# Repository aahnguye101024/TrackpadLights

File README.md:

# TrackpadLights
This project tests out a trackpad IC that I found interesting and creates a light that follows your finger input based on the "trackpad" board. 

## Main Board

## Cap Touch Board

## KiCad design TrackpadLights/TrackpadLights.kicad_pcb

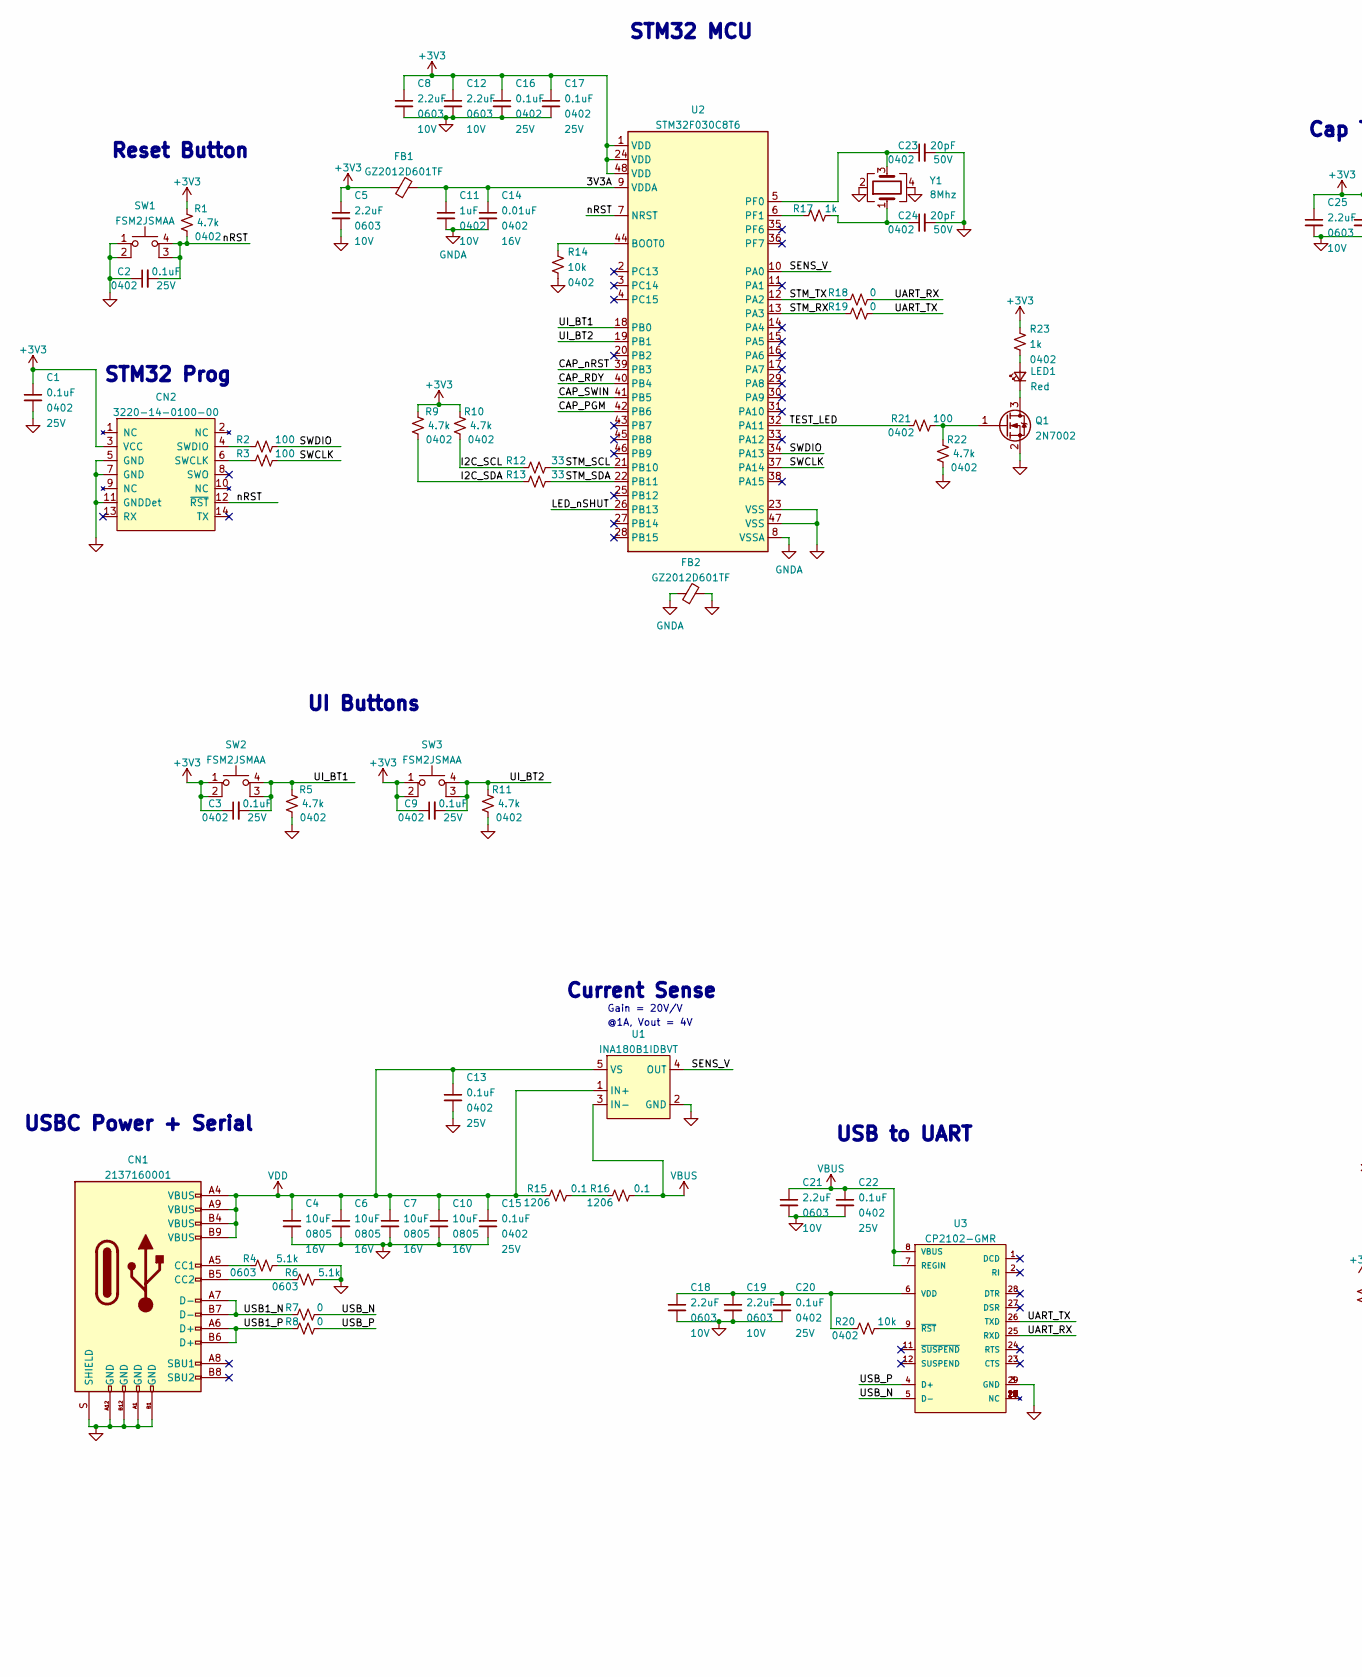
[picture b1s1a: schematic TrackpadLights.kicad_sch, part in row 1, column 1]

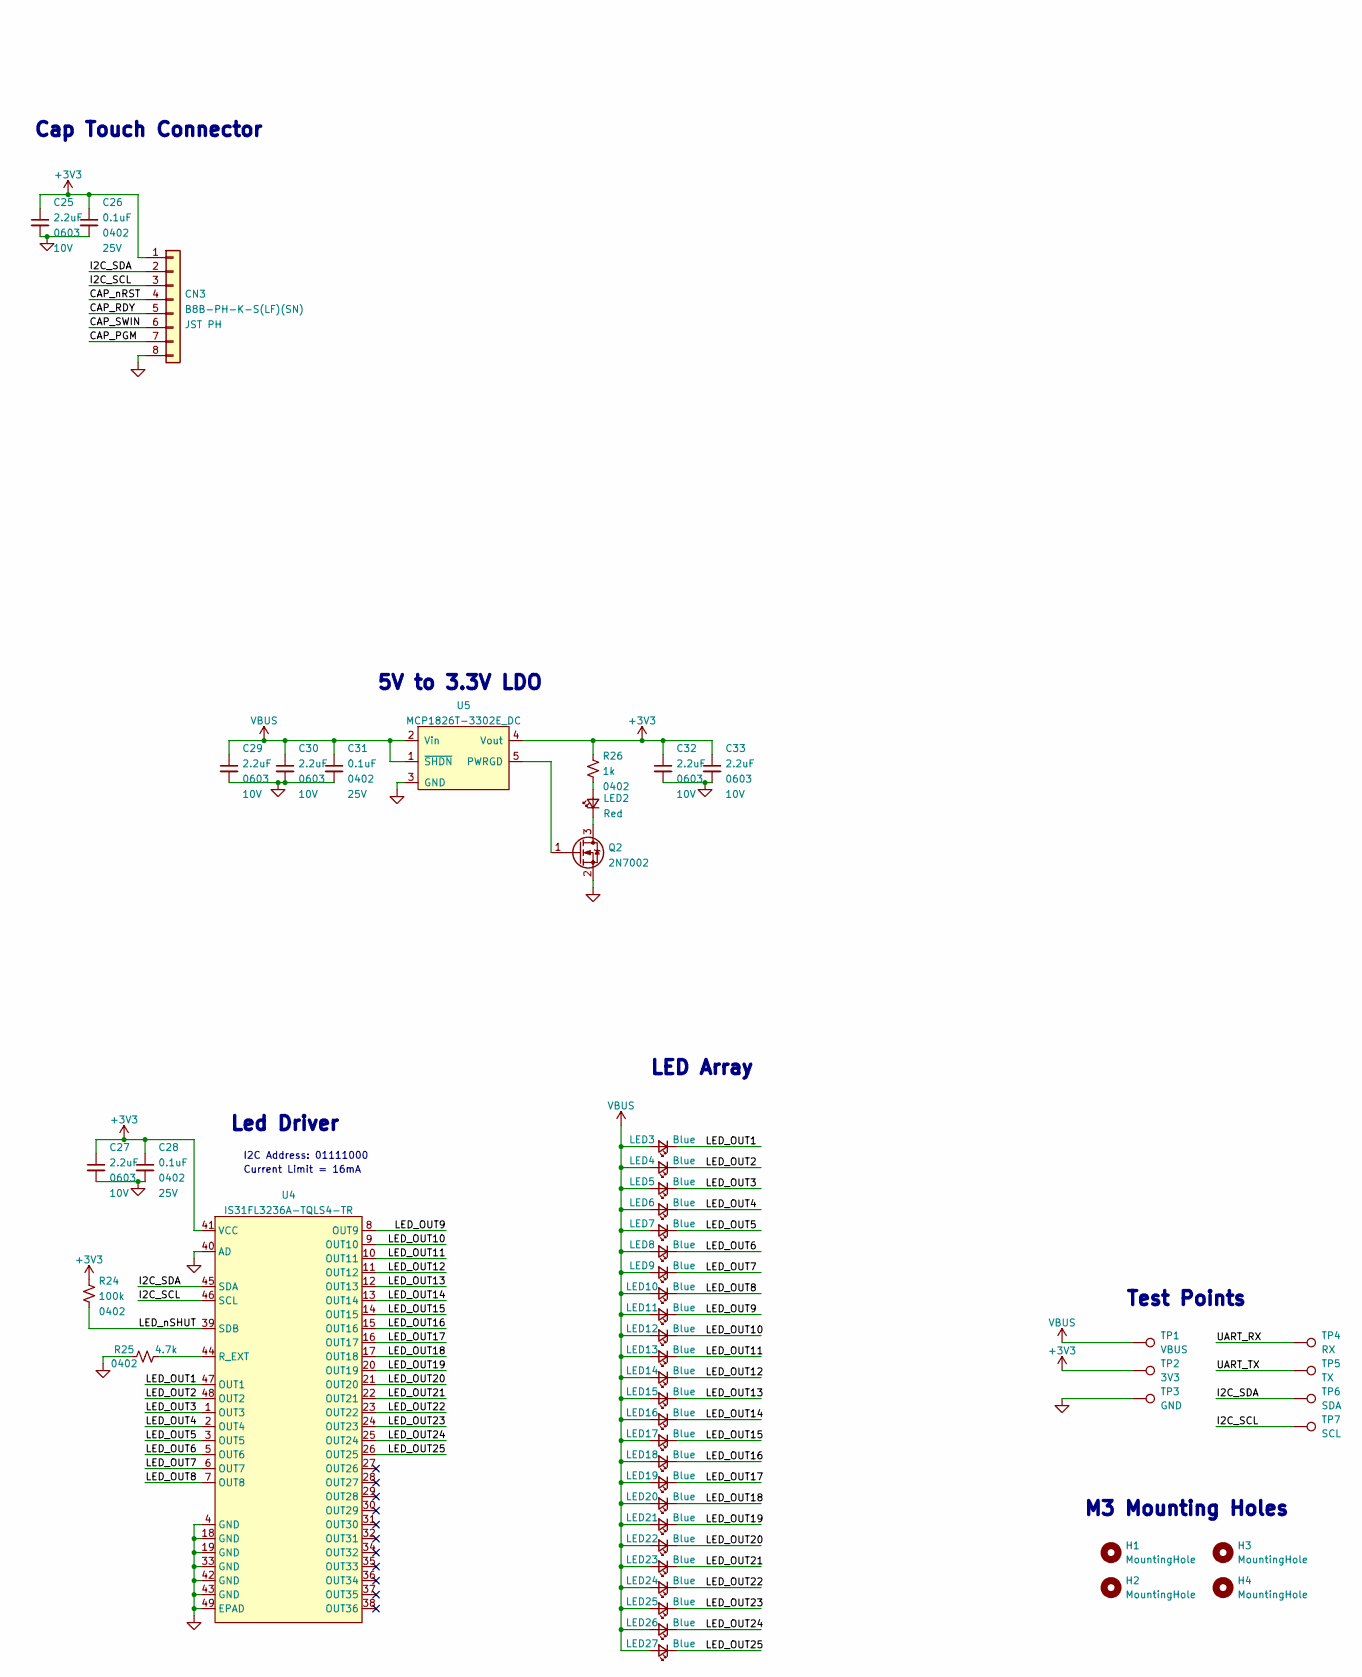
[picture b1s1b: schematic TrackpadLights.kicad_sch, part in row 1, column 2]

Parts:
C1, C2, C3, C9, C13, C15, C16, C17, C20, C22, C26, C28, C31: 0.1uF; C_0402_1005Metric; Voltage 25V; Part Number 1276-1043-1-ND; JLCPCB Yes
C4, C6, C7, C10: 10uF; C_0805_2012Metric; Voltage 16V; Part Number 1276-2893-1-ND; JLCPCB Yes
C5, C8, C12, C18, C19, C21, C25, C27, C29, C30, C32, C33: 2.2uF; C_0603_1608Metric; Voltage 10V; Part Number 1276-1085-1-ND; JLCPCB Yes
C11: 1uF; C_0402_1005Metric; Voltage 10V; Part Number 1276-1076-1-ND; JLCPCB Yes
C14: 0.01uF; C_0402_1005Metric; Voltage 16V; Part Number 478-0402YD103KAT2ACT-ND; JLCPCB Yes
C23, C24: 20pF; C_0402_1005Metric; Voltage 50V; Part Number 1276-1661-1-ND; JLCPCB Yes
CN1: 2137160001; Part Number Personal
CN2: 3220-14-0100-00; Part Number Personal
CN3: B8B-PH-K-S(LF)(SN); JST_PH_B8B-PH-K_1x08_P2.00mm_Vertical; Part Number 455-1710-ND
FB1, FB2: GZ2012D601TF; L_0805_2012Metric; Part Number C1017; JLCPCB Yes
H1, H2, H3, H4: MountingHole; MountingHole_3.2mm_M3_ISO7380
LED1, LED2: NCD0805R1; LED_0805_2012Metric; Part Number C84256
LED3, LED4, LED5, LED6, LED7, LED8, LED9, LED10, LED11, LED12, LED13, LED14, LED15, LED16, LED17, LED18, LED19, LED20, LED21, LED22, LED23, LED24, LED25, LED26, LED27: 19-213SUBC/S400-A5/S208-2/TR8; LED_0603_1608Metric; Part Number 1080-1581-1-ND; JLCPCB Yes
Q1, Q2: 2N7002; SOT-23; Part Number C8545; JLC Part Number C8545
R1, R5, R9, R10, R11, R22, R25: 4.7k; R_0402_1005Metric; Part Number RMCF0402FT4K70CT-ND; JLCPCB Yes
R2, R3, R21: 100; R_0402_1005Metric; Part Number RMCF0402FT100RCT-ND; JLCPCB Yes
R4, R6: 5.1k_0603; R_0603_1608Metric; Part Number RMCF0603FT5K10CT-ND; JLCPCB Yes
R7, R8, R18, R19: 0; R_0402_1005Metric; Part Number RMCF0402ZT0R00CT-ND; JLCPCB Yes
R12, R13: 33; R_0402_1005Metric; Part Number 311-33.0LRCT-ND; JLCPCB Yes
R14: 10k; R_0402_1005Metric; Part Number RMCF0402FT10K0CT-ND
R15, R16: 0.1; R_1206_3216Metric; Part Number CSR1206FTR100CT-ND; JLCPCB Yes
R17, R23, R26: 1k; R_0402_1005Metric; Part Number RMCF0402FT1K00CT-ND; JLCPCB Yes
R20: 10k; R_0402_1005Metric; Part Number RMCF0402FT10K0CT-ND; JLCPCB Yes
R24: 100k; R_0402_1005Metric; Part Number 2037-PFR05S-104-FNHCT-ND; JLCPCB Yes
SW1, SW2, SW3: FSM2JSMAA; SW_2-1437565-8; Part Number Personal
TP1: VBUS; CurrentTestPoint
TP2: 3V3; CurrentTestPoint
TP3: GND; CurrentTestPoint
TP4: RX; CurrentTestPoint
TP5: TX; CurrentTestPoint
TP6: SDA; CurrentTestPoint
TP7: SCL; CurrentTestPoint
U1: INA180B1IDBVT; SOT-23-5; Part Number 296-46631-1-ND
U2: STM32F030C8T6; LQFP-48_7x7mm_P0.5mm; JLCPCB Yes
U3: CP2102-GMR; QFN28G_0.5-5X5MM; Part Number IC USB-TO-UART BRIDGE 28VQFN; JLC Part Number C6568
U4: IS31FL3236A-TQLS4-TR; TQFP-48-1EP_7x7mm_P0.5mm_EP5x5mm; Part Number 2521-IS31FL3236A-TQLS4-TRCT-ND
U5: MCP1826T-3302E_DC; SOT-223-6_TabPin3; Part Number MCP1826T-3302E/DCCT-ND
Y1: ECS-80-18-33-JGN-TR; XTAL_ECS-240-8-33-AGN-TR; Part Number Personal

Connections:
+3V3: C1.1, C3.1, C5.1, C8.1, C9.1, C12.1, C16.1, C17.1, C25.1, C26.1, C27.1, C28.1, C32.1, C33.1, CN2.3 (VCC), CN3.1, FB1.1, R1.2, R9.2, R10.2, R23.1, R24.1, R26.1, SW2.1, SW2.2, SW3.1, SW3.2, TP2.1, U2.1 (VDD), U2.24 (VDD), U2.48 (VDD), U4.41 (VCC), U5.4 (Vout)
/3V3A: C11.1, C14.1, FB1.2, U2.9 (VDDA)
/CAP_PGM: CN3.7, U2.42 (PB6)
/CAP_RDY: CN3.5, U2.40 (PB4)
/CAP_SWIN: CN3.6, U2.41 (PB5)
/CAP_nRST: CN3.4, U2.39 (PB3)
/I2C_SCL: CN3.3, R10.1, R12.1, TP7.1, U4.46 (SCL)
/I2C_SDA: CN3.2, R9.1, R13.1, TP6.1, U4.45 (SDA)
/LED_OUT1: LED3.1 (K), U4.47 (OUT1)
/LED_OUT2: LED4.1 (K), U4.48 (OUT2)
/LED_OUT3: LED5.1 (K), U4.1 (OUT3)
/LED_OUT4: LED6.1 (K), U4.2 (OUT4)
/LED_OUT5: LED7.1 (K), U4.3 (OUT5)
/LED_OUT6: LED8.1 (K), U4.5 (OUT6)
/LED_OUT7: LED9.1 (K), U4.6 (OUT7)
/LED_OUT8: LED10.1 (K), U4.7 (OUT8)
/LED_OUT9: LED11.1 (K), U4.8 (OUT9)
/LED_OUT10: LED12.1 (K), U4.9 (OUT10)
/LED_OUT11: LED13.1 (K), U4.10 (OUT11)
/LED_OUT12: LED14.1 (K), U4.11 (OUT12)
/LED_OUT13: LED15.1 (K), U4.12 (OUT13)
/LED_OUT14: LED16.1 (K), U4.13 (OUT14)
/LED_OUT15: LED17.1 (K), U4.14 (OUT15)
/LED_OUT16: LED18.1 (K), U4.15 (OUT16)
/LED_OUT17: LED19.1 (K), U4.16 (OUT17)
/LED_OUT18: LED20.1 (K), U4.17 (OUT18)
/LED_OUT19: LED21.1 (K), U4.20 (OUT19)
/LED_OUT20: LED22.1 (K), U4.21 (OUT20)
/LED_OUT21: LED23.1 (K), U4.22 (OUT21)
/LED_OUT22: LED24.1 (K), U4.23 (OUT22)
/LED_OUT23: LED25.1 (K), U4.24 (OUT23)
/LED_OUT24: LED26.1 (K), U4.25 (OUT24)
/LED_OUT25: LED27.1 (K), U4.26 (OUT25)
/LED_nSHUT: R24.2, U2.26 (PB13), U4.39 (SDB)
/SENS_V: U1.4 (OUT), U2.10 (PA0)
/STM_RX: R19.1, U2.13 (PA3)
/STM_SCL: R12.2, U2.21 (PB10)
/STM_SDA: R13.2, U2.22 (PB11)
/STM_TX: R18.1, U2.12 (PA2)
/SWCLK: R3.2, U2.37 (PA14)
/SWDIO: R2.2, U2.34 (PA13)
/TEST_LED: R21.1, U2.32 (PA11)
/UART_RX: R18.2, TP4.1, U3.25 (RXD)
/UART_TX: R19.2, TP5.1, U3.26 (TXD)
/UI_BT1: C3.2, R5.2, SW2.3 (K), SW2.4 (A), U2.18 (PB0)
/UI_BT2: C9.2, R11.2, SW3.3 (K), SW3.4 (A), U2.19 (PB1)
/USB1_N: CN1.A7 (D-), CN1.B7 (D-), R7.1
/USB1_P: CN1.A6 (D+), CN1.B6 (D+), R8.1
/USB_N: R7.2, U3.5 (D-)
/USB_P: R8.2, U3.4 (D+)
/nRST: C2.2, CN2.12 (~RST), R1.1, SW1.3 (K), SW1.4 (A), U2.7 (NRST)
GND: C1.2, C2.1, C4.2, C5.2, C6.2, C7.2, C8.2, C10.2, C12.2, C13.2, C15.2, C16.2, C17.2, C18.2, C19.2, C20.2, C21.2, C22.2, C23.2, C24.2, C25.2, C26.2, C27.2, C28.2, C29.2, C30.2, C31.2, C32.2, C33.2, CN1.A1 (GND), CN1.A12 (GND), CN1.B1 (GND), CN1.B12 (GND), CN1.S (SHIELD), CN2.5 (GND), CN2.7 (GND), CN2.11 (GNDDet), CN3.8, FB2.2, Q1.2 (S), Q2.2 (S), R4.2, R5.1, R6.2, R11.1, R14.2, R22.1, R25.1, SW1.1, SW1.2, TP3.1, U1.2 (GND), U2.23 (VSS), U2.47 (VSS), U3.3 (GND), U3.29 (GND), U4.4 (GND), U4.18 (GND), U4.19 (GND), U4.33 (GND), U4.40 (AD), U4.42 (GND), U4.43 (GND), U4.49 (EPAD), U5.3 (GND), Y1.2, Y1.4
GNDA: C11.2, C14.2, FB2.1, U2.8 (VSSA)
unnamed: C18.1, C19.1, C20.1, R20.1, U3.6 (VDD)
unnamed: C23.1, U2.5 (PF0), Y1.3
unnamed: C24.1, R17.2, Y1.1
unnamed: CN1.A5 (CC1), R4.1
unnamed: CN1.B5 (CC2), R6.1
unnamed: CN2.4 (SWDIO), R2.1
unnamed: CN2.6 (SWCLK), R3.1
unnamed: LED1.1 (K), Q1.3 (D)
unnamed: LED1.2 (A), R23.2
unnamed: LED2.1 (K), Q2.3 (D)
unnamed: LED2.2 (A), R26.2
unnamed: Q1.1 (G), R21.2, R22.2
unnamed: Q2.1 (G), U5.5 (PWRGD)
unnamed: R14.1, U2.44 (BOOT0)
unnamed: R15.2, R16.1
unnamed: R17.1, U2.6 (PF1)
unnamed: R20.2, U3.9 (~RST)
unnamed: R25.2, U4.44 (R_EXT)
VBUS: C21.1, C22.1, C29.1, C30.1, C31.1, LED3.2 (A), LED4.2 (A), LED5.2 (A), LED6.2 (A), LED7.2 (A), LED8.2 (A), LED9.2 (A), LED10.2 (A), LED11.2 (A), LED12.2 (A), LED13.2 (A), LED14.2 (A), LED15.2 (A), LED16.2 (A), LED17.2 (A), LED18.2 (A), LED19.2 (A), LED20.2 (A), LED21.2 (A), LED22.2 (A), LED23.2 (A), LED24.2 (A), LED25.2 (A), LED26.2 (A), LED27.2 (A), R16.2, TP1.1, U1.3 (IN-), U3.7 (REGIN), U3.8 (VBUS), U5.1 (~SHDN), U5.2 (Vin)
VDD: C4.1, C6.1, C7.1, C10.1, C13.1, C15.1, CN1.A4 (VBUS), CN1.A9 (VBUS), CN1.B4 (VBUS), CN1.B9 (VBUS), R15.1, U1.1 (IN+), U1.5 (VS)

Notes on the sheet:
Reset Button
STM32 MCU
Current Sense
UI Buttons
Led Driver
Gain = 20V/V
@1A, Vout = 4V
I2C Address: 01111000
5V to 3.3V LDO
USB to UART
Cap Touch Connector
STM32 Prog
LED Array
Current Limit = 16mA
USBC Power + Serial
Test Points
M3 Mounting Holes

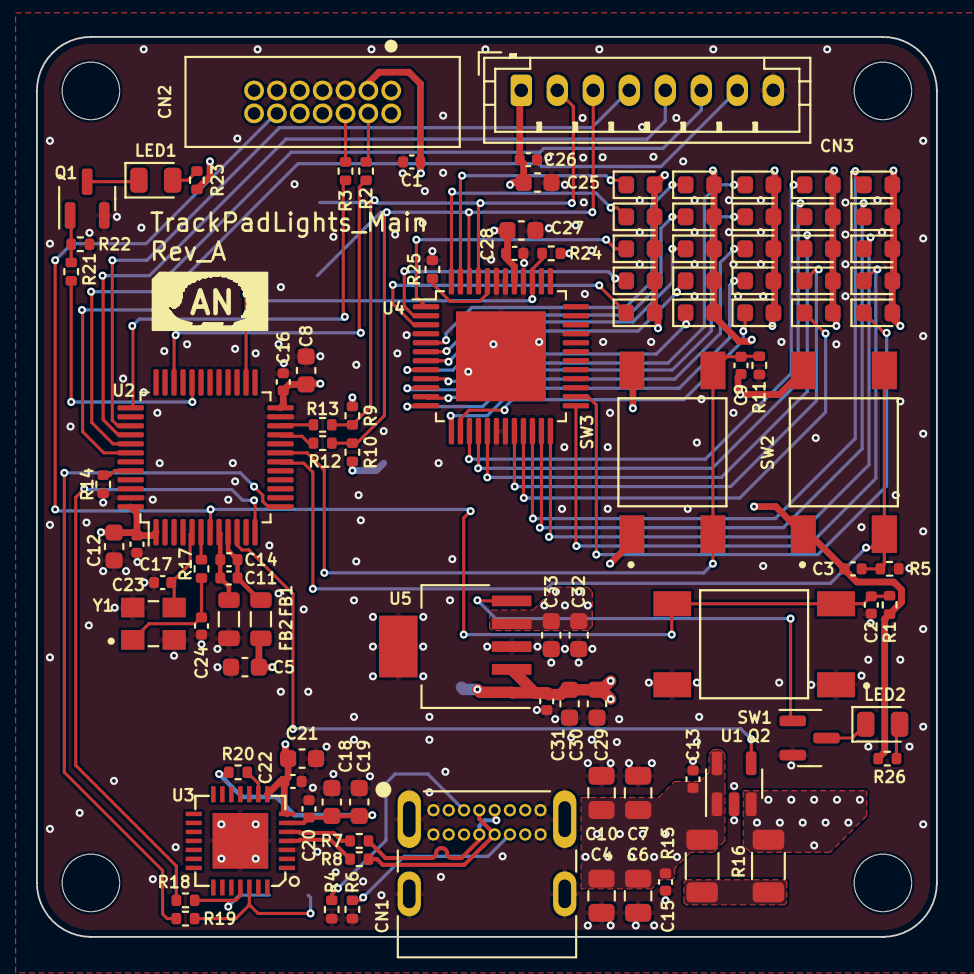
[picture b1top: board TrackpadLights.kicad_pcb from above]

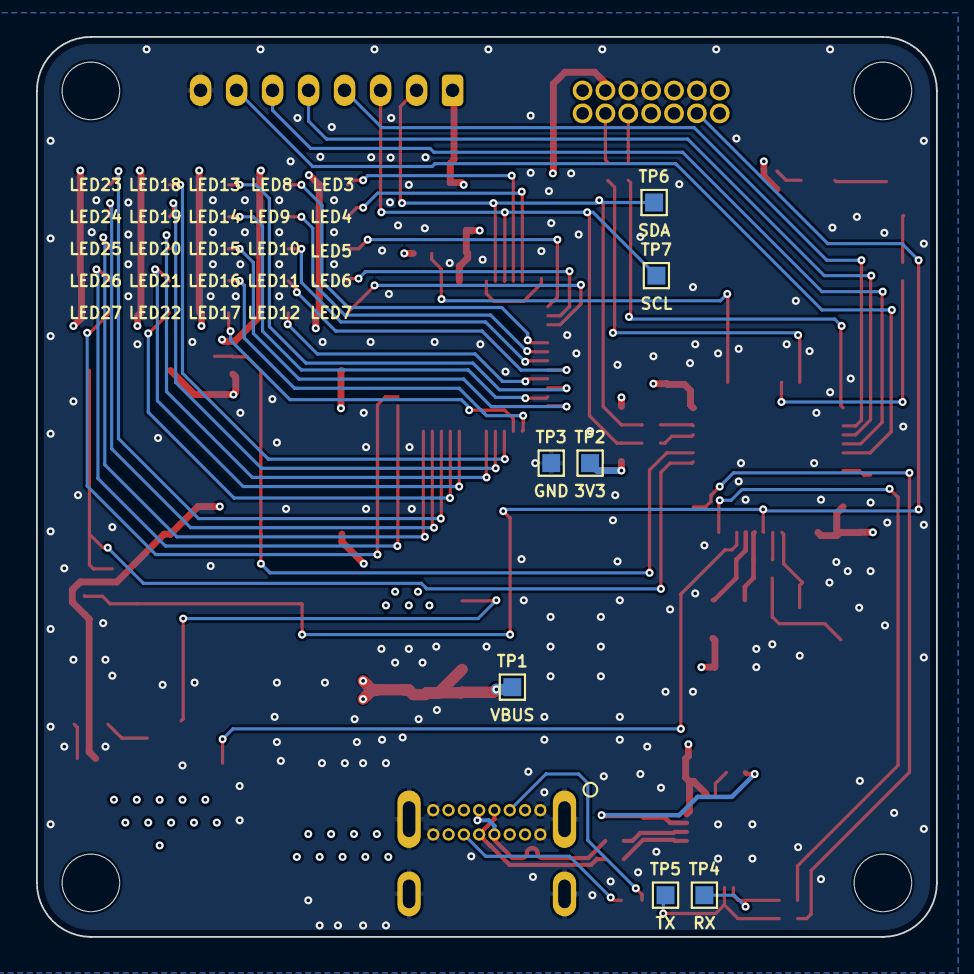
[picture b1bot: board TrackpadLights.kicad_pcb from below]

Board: 4 copper layers, 50.0 x 50.0 mm, 113 parts (7 on the bottom side), 73 nets.

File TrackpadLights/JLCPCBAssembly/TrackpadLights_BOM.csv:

Comment,Designator,Footprint,JLCPCB Part #（optional）
0.1uF,"C1, C2, C3, C9, C13, C15, C16, C17, C20, C22, C26, C28, C31, ",,C307331
10uF,"C4, C6, C7, C10, ",,C15850
2.2uF,"C5, C8, C12, C18, C19, C21, C25, C27, C29, C30, C32, C33, ",,C23630
1uF,"C11, ",,C52923
0.01uF,"C14, ",,C15195
20pF,"C23, C24, ",,C1554
GZ2012D601TF,"FB1, FB2, ",,C1017
19-213SUBC/S400-A5/S208-2/TR8,"LED3, LED4, LED5, LED6, LED7, LED8, LED9, LED10, LED11, LED12, LED13, LED14, LED15, LED16, LED17, LED18, LED19, LED20, LED21, LED22, LED23, LED24, LED25, LED26, LED27, ",,C72041
2N7002,"Q1, Q2, ",,C8545
4.7k,"R1, R5, R9, R10, R11, R22, R25, ",,C25900
100,"R2, R3, R21, ",,C25076
5.1k,"R4, R6, ",,C23186
0,"R7, R8, R18, R19, ",,C17168
33,"R12, R13, ",,C25105
10k,"R14, R20, ",,C25744
0.1,"R15, R16, ",,C25334
100k,"R24, ",,C25741
STM32F030C8T6,"U2, ",,C23922
CP2102-GMR,"U3, ",,C6568
1k,"R17, R23, R26, ",,C11702

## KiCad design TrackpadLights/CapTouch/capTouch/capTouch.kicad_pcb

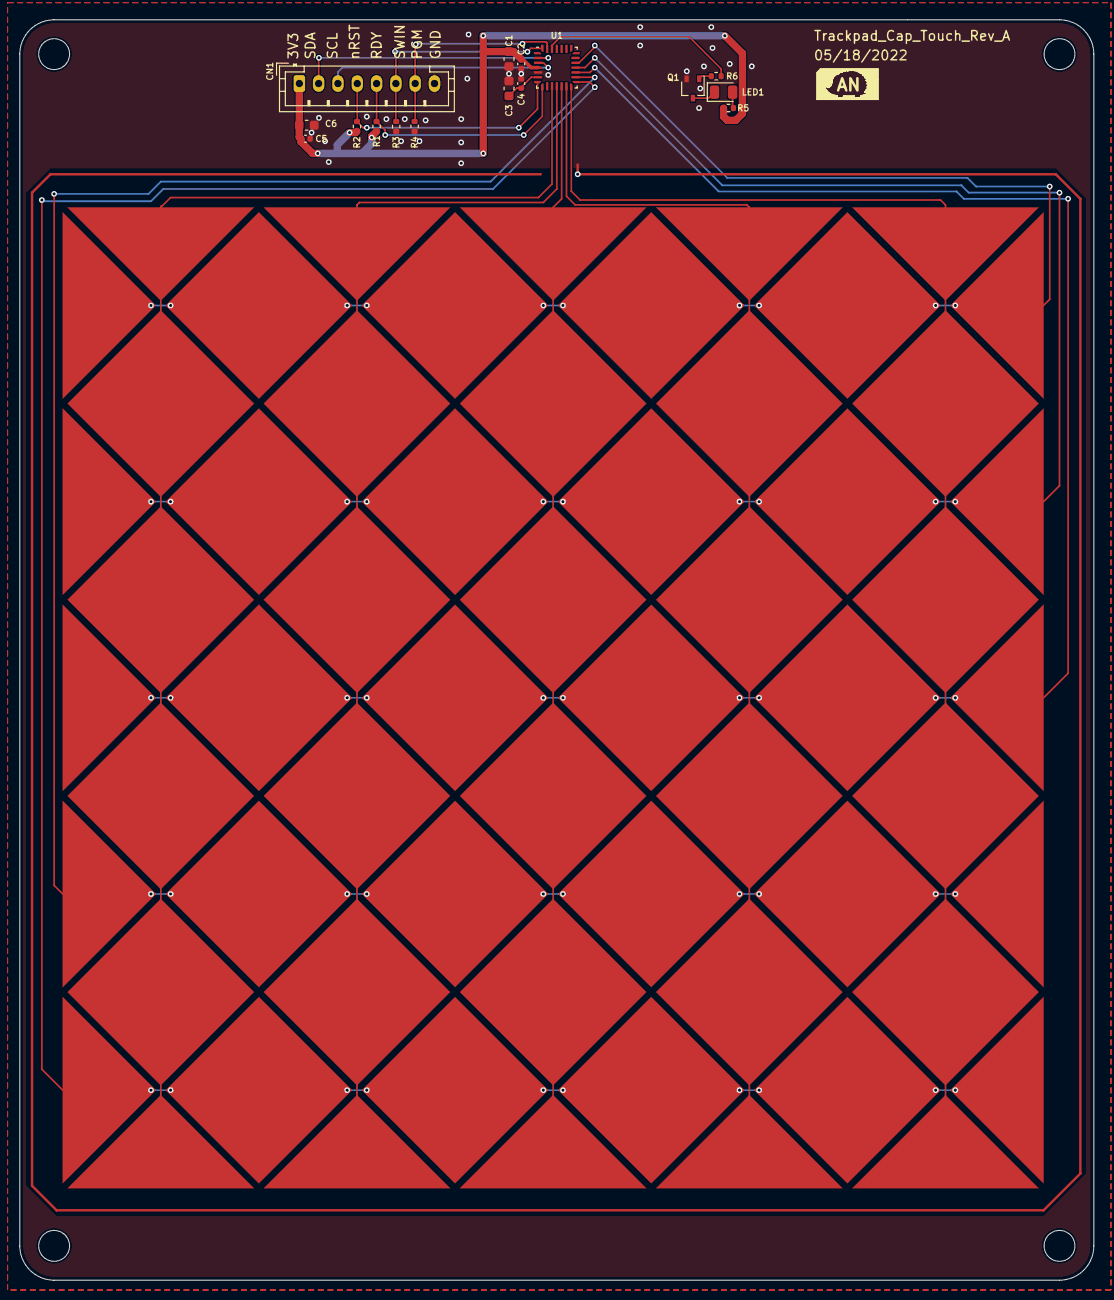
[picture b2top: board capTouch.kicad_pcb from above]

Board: 2 copper layers, 111.3 x 130.6 mm, 80 parts (0 on the bottom side), 23 nets.

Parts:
C1, C3, C6: 2.2uF; C_0603_1608Metric
C2, C4, C5: 0.1uF; C_0402_1005Metric
CN1: B8B-PH-K-S(LF)(SN); JST_PH_B8B-PH-K_1x08_P2.00mm_Vertical
H1, H2, H3, H4: MountingHole; MountingHole_3.2mm_M3_ISO7380
LED1: NCD0805R1; LED_0805_2012Metric
Q1: BSS138BKW,115; SOT-323_SC-70
R1, R2, R3, R4: 4.7k; R_0402_1005Metric
R5: 1k; R_0402_1005Metric
R6: 100; R_0402_1005Metric
TP1, TP2, TP3, TP4, TP5, TP6, TP7, TP8, TP9, TP10, TP41, TP42, TP43, TP44, TP45, TP46, TP47, TP48, TP49, TP50: TestPoint; IQS525-BL-QNR_Side
TP11, TP12, TP13, TP14, TP15, TP16, TP17, TP18, TP19, TP20, TP21, TP22, TP23, TP24, TP25, TP26, TP27, TP28, TP29, TP30, TP31, TP32, TP33, TP34, TP35, TP36, TP37, TP38, TP39, TP40, TP51, TP52, TP53, TP54, TP55, TP56, TP57, TP58, TP59, TP60: TestPoint; IQS525-BL-QNR_Diamond
U1: IQS525-BL-QNR; QFN-28_4x4mm_P0.5mm

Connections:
+3V3: C1.1, C2.1, C5.1, C6.1, CN1.1, R1.2, R2.2, R5.1, U1.4 (VDDHI)
/CAP_PGM: CN1.7, R4.2, U1.27 (PGM)
/CAP_RDY: CN1.5, R1.1, U1.8 (RDY)
/CAP_SWIN: CN1.6, R3.2, U1.28 (SW_IN)
/CAP_nRST: CN1.4, R2.1, U1.7 (NRST)
/I2C_SCL: CN1.3, U1.3 (SCL)
/I2C_SDA: CN1.2, U1.2 (SDA)
/RX0: TP1.1, TP11.1, TP21.1, TP31.1, TP41.1, TP51.1, U1.10 (RX0)
/RX1: TP2.1, TP12.1, TP22.1, TP32.1, TP42.1, TP52.1, U1.11 (RX1)
/RX2: TP3.1, TP13.1, TP23.1, TP33.1, TP43.1, TP53.1, U1.12 (RX2)
/RX3: TP4.1, TP14.1, TP24.1, TP34.1, TP44.1, TP54.1, U1.13 (RX3)
/RX4: TP5.1, TP15.1, TP25.1, TP35.1, TP45.1, TP55.1, U1.14 (RX4)
/TX0: TP6.1, TP16.1, TP26.1, TP36.1, TP46.1, TP56.1, U1.19 (TX0)
/TX1: TP7.1, TP17.1, TP27.1, TP37.1, TP47.1, TP57.1, U1.18 (TX1)
/TX2: TP8.1, TP18.1, TP28.1, TP38.1, TP48.1, TP58.1, U1.17 (RX7/TX2)
/TX3: TP9.1, TP19.1, TP29.1, TP39.1, TP49.1, TP59.1, U1.16 (RX6/TX3)
/TX4: TP10.1, TP20.1, TP30.1, TP40.1, TP50.1, TP60.1, U1.15 (RX5/TX4)
GND: C1.2, C2.2, C3.2, C4.2, C5.2, C6.2, CN1.8, Q1.2 (S), R3.1, R4.1, U1.5 (VSS)
unnamed: C3.1, C4.1, U1.6 (VREG)
unnamed: LED1.1 (K), Q1.3 (D)
unnamed: LED1.2 (A), R5.2
unnamed: R6.1, U1.26 (PB0)
unnamed: Q1.1 (G), R6.2

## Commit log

2024-01-31 initial push
2024-01-31 Added whole new board
2024-01-31 Updated Read me
